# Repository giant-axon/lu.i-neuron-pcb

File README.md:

# Lu.i[¹](#footnote-1) – An educational neuron PCB

Lu.i is an electronic neuron circuit mimicking and illustrating the basic dynamics of real, biological neurons.
The printed circuit board (PCB) features a configurable, fully analog implementation of the leaky integrate-and-fire model and visualizes the internal state, the *membrane potential*, through a VU-meter-style chain of LEDs.
The neuron emits a short pulse whenever the membrane potential crosses a predefined threshold voltage.
Neurons communicate by exchanging these *spikes*.
Multiple boards can be connected via jumper wires to form networks.

<br/>

For a more detailed write-up you may refer to our manuscript:

**Lu. i – A low-cost electronic neuron for education and outreach**  
Yannik Stradmann, Julian Göltz, Mihai A. Petrovici, Johannes Schemmel, Sebastian Billaudelle (2025)  
Trends in Neuroscience and Education, Volume 38, 100248: [10.1016/j.tine.2025.100248](https://doi.org/10.1016/j.tine.2025.100248)

For inquiries feel free to contact us at [info@giantaxon.org](mailto:info@giantaxon.org).

## Features
- fully analog implementation of the leaky integrate-and-fire model
- configurable leak potential and membrane time constant
- three synapses with tunable weight and sign (excitatory or inhibitory) and shared synaptic time constant
- three output terminals to forward spikes to other neurons
- powered by a CR2032 coin battery
- Arduino-compatible (5V-tolerant spike IO)
- VU-meter-style visualization of the membrane potential and spike LED
- optimized for low-cost production (~ 3 € per neuron)

## Example Networks
Resembling the structure of the nervous system, multiple *Lu.i* boards can be connected to form complex neural networks.
They may be used for illustrative purposes, mimicking biological behavior, or even solving functional tasks.
The following hierarchical network, e.g., implements an *exclusive OR* (XOR).

For a more extensive list of example networks please refer to [Lu.i's documentation](doc/).

## Model
The neuron implemented on the PCBs is called Leaky Integrate-and-Fire (LIF) model.
For this model, the membrane voltage follows the dynamics described by the differential equation

$$
    \tau_\text{mem} \frac{\mathrm{d}V_\text{mem}}{\mathrm{d}t} = - \left(V_\text{mem} - V_\text{leak} \right) + I_{\text{syn}} / g_\text{leak}.
$$

In short, the neuron sums up its input $I_\text{syn}$ and decays back to the leak voltage $V_\text{leak}$.
The LIF model, including the spiking behavior when the threshold is reached, is implemented in electric circuits.

## Electronic Implementation
The following circuit diagram shows the different functional blocks of the analog implementation on *Lu.i*.
The full schematics are given as KiCAD design files.

Besides the formation of synaptic connections between the individual neurons, inputs and outputs of each *Lu.i* can also be used to connect with a wide range of microcontrollers and sensors.
Example code can be found in the [documentation](doc/). 

## Manufacturing
The component choice in the *Lu.i* design is optimized for manufacturing at [JLCPCB](https://jlcpcb.com/).
With every [release](../../releases/), we include all the design files necessary for production.
Detailed instructions on the ordering process can be found in the [documentation](doc/).

---

<a name="footnote-1">¹</a> The name »Lu.i« (phonetic notation of »Louis«) is a tribute to Louis E. Lapicque, who first formulated the leaky integrate-and-fire equations modeling the dynamics of a neuron.

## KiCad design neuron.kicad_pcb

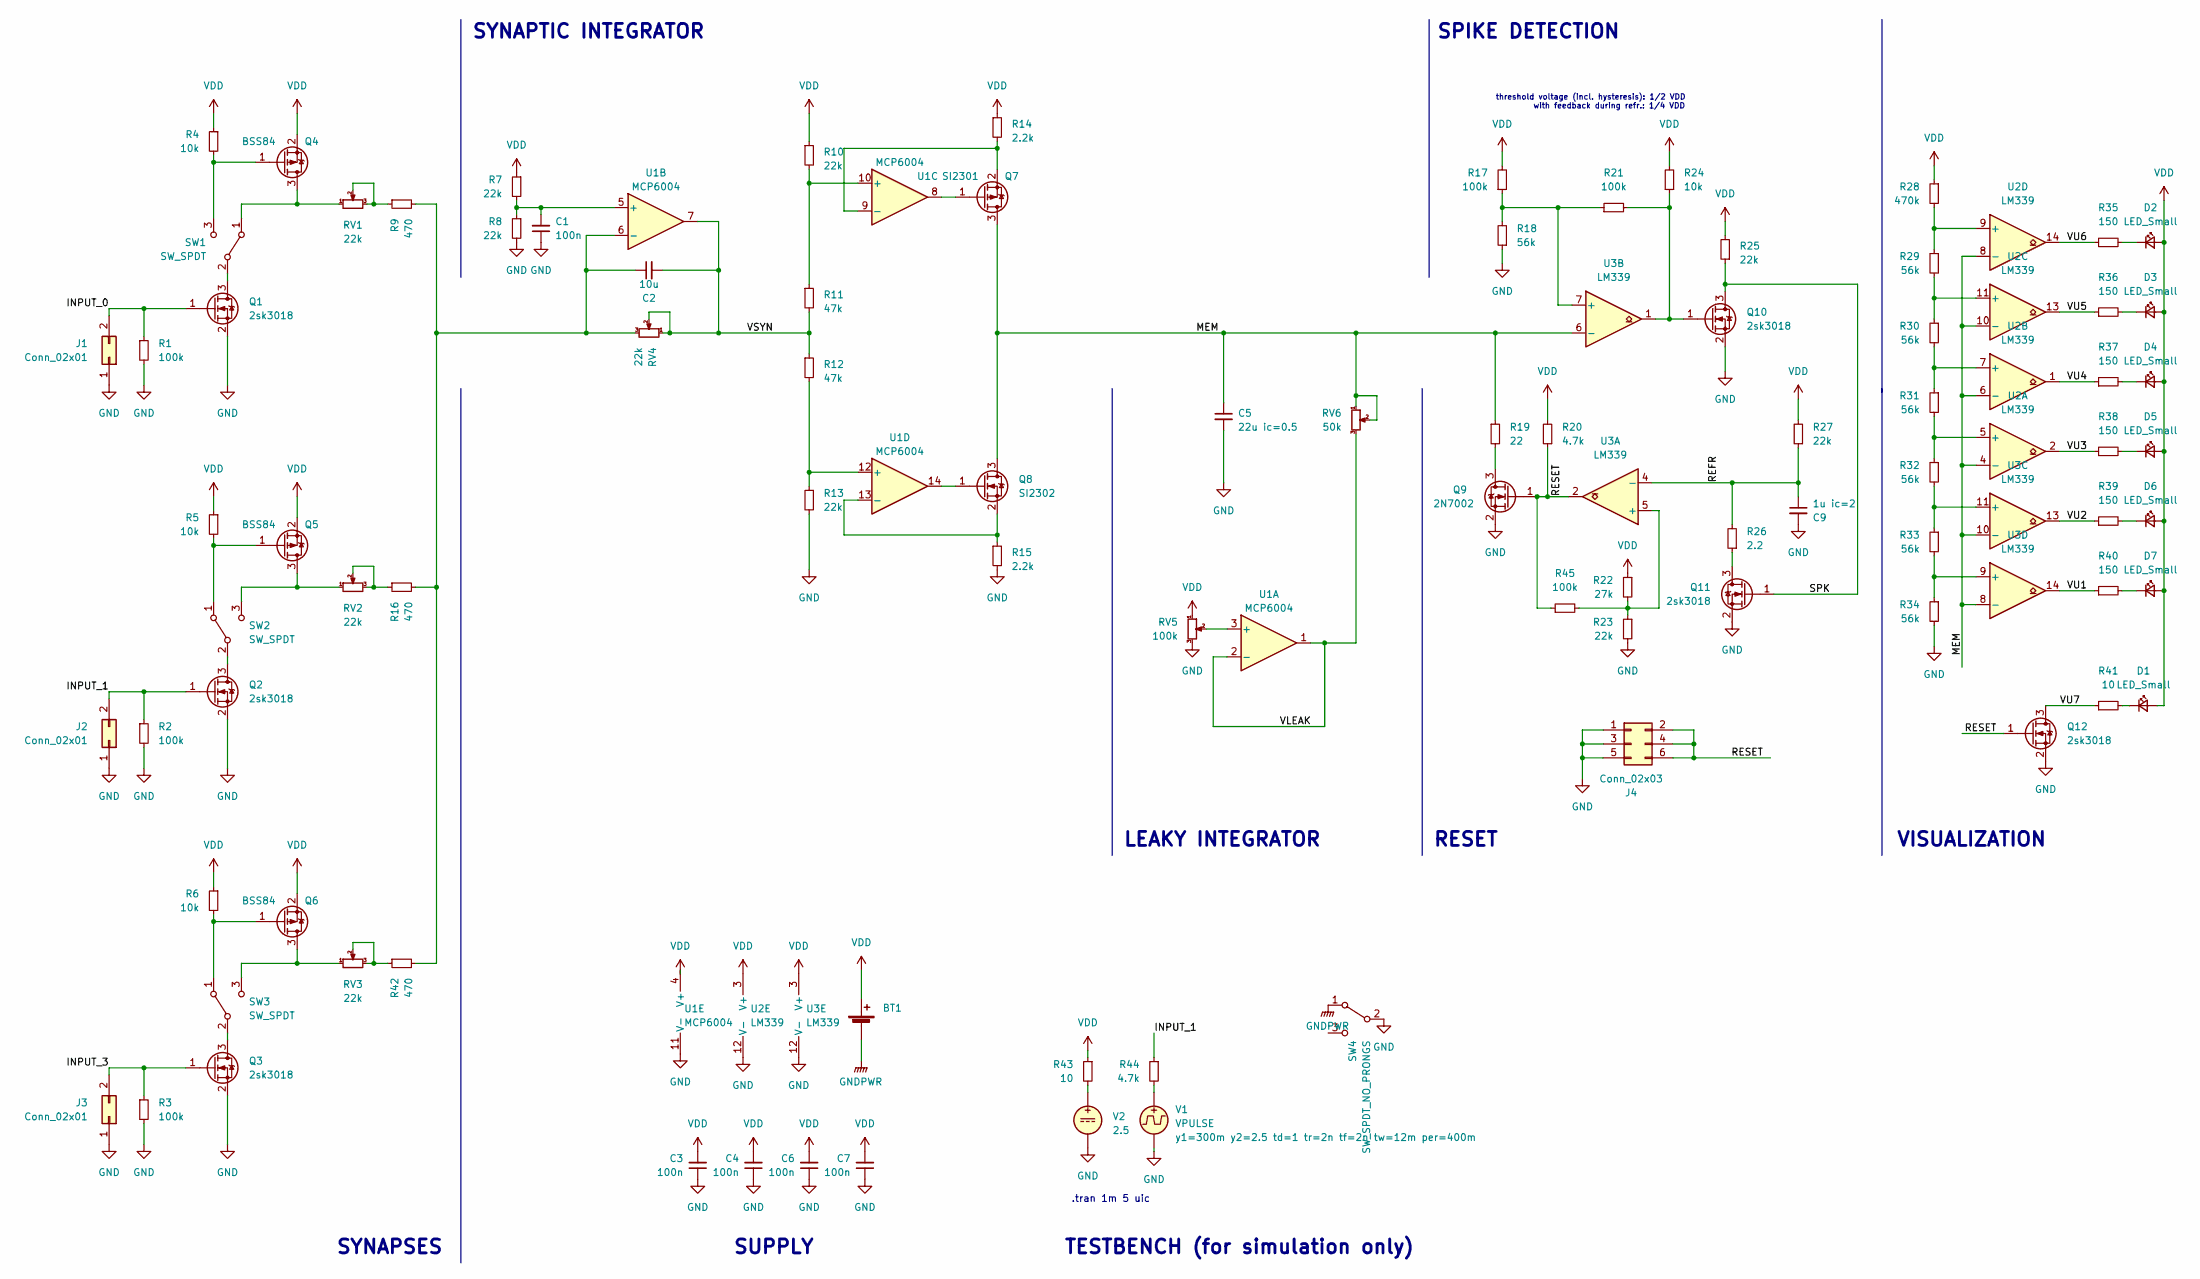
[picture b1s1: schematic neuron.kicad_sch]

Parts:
BT1: type="R" model="Battery_Cell" lib=""; CR2032_Holder; LCSC C70377
C1, C3, C4, C6, C7: 100n; C_0402_1005Metric; LCSC C1525
C2: 10u; C_0402_1005Metric; LCSC C15525
C5: 22u ic=0.5; C_0402_1005Metric; LCSC C415703
C9: 1u ic=2; C_0402_1005Metric; LCSC C52923
D1, D2, D3, D4, D5, D6, D7: LED_Small; LED_0402_1005Metric; LCSC C779450
J1, J2, J3: Conn_02x01; PinHeader_1x02_P2.54mm_Vertical; LCSC C2894925
J4: Conn_02x03; PinHeader_2x03_P2.54mm_Vertical; LCSC C492420
Q1, Q2, Q3, Q10, Q11, Q12: 2sk3018; SOT-23; LCSC C181084
Q4, Q5, Q6: BSS84; SOT-23; LCSC C8492
Q7: SI2301; SOT-23; LCSC C10487
Q8: SI2302; SOT-23; LCSC C10488
Q9: 2N7002; SOT-23; LCSC C8545
R1, R2, R3, R17, R21, R45: 100k; R_0402_1005Metric; LCSC C25741
R4, R5, R6, R24: 10k; R_0402_1005Metric; LCSC C25744
R7, R8, R10, R13: 22k; R_0402_1005Metric; LCSC C326601
R9, R16, R42: 470; R_0402_1005Metric; LCSC C25117
R11, R12: 47k; R_0402_1005Metric; LCSC C5152005
R14, R15: 2.2k; R_0402_1005Metric; LCSC C705646
R18, R29, R30, R31, R32, R33, R34: 56k; R_0402_1005Metric; LCSC C25796
R19: 22; R_0402_1005Metric; LCSC C25092
R20: 4.7k; R_0402_1005Metric; LCSC C25900
R22: 27k; R_0402_1005Metric; LCSC C25771
R23, R25, R27: 22k; R_0402_1005Metric; LCSC C25768
R26: 2.2; R_0402_1005Metric; LCSC C25101
R28: 470k; R_0402_1005Metric; LCSC C25790
R35, R36, R37, R38, R39, R40: 150; R_0402_1005Metric; LCSC C25082
R41: 10; R_0402_1005Metric; LCSC C25077
R43: 10; R_0402_1005Metric; LCSC C25768
R44: 4.7k; R_0402_1005Metric; LCSC C25768
RV1, RV2, RV3, RV4: 22k; Potentiometer; LCSC C128552
RV5: 100k; Potentiometer; LCSC C128545
RV6: 50k; Potentiometer; LCSC C145161
SW1, SW2, SW3: SW_SPDT; K3-1296S-E1; LCSC C128955
SW4: SW_SPDT_NO_PRONGS; SSAJ120100; LCSC C160864
U1: MCP6004; TSSOP-14_4.4x5mm_P0.65mm; LCSC C50282
U2, U3: LM339; TSSOP-14_4.4x5mm_P0.65mm; LCSC C42184
V1: VPULSE
V2: 2.5

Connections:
/INPUT_0: J1.2, Q1.1 (G), R1.1
/INPUT_1: J2.2, Q2.1 (G), R2.1, R44.1
/INPUT_3: J3.2, Q3.1 (G), R3.1
/MEM: C5.1, Q7.3 (D), Q8.3 (D), R19.1, RV6.1, RV6.2, U2.4 (-), U2.6 (-), U2.8 (-), U2.10 (-), U3.6 (-), U3.8 (-), U3.10 (-)
/REFR: C9.1, R26.2, R27.1, U3.4 (-)
/RESET: J4.2, J4.4, J4.6, Q9.1 (G), Q12.1 (G), R20.1, R45.1, U3.2
/SPK: Q10.3 (D), Q11.1 (G), R25.1
/VLEAK: RV6.3, U1.1, U1.2 (-)
/VSYN: C2.2, R11.2, R12.1, RV4.1, RV4.2, U1.7
/VU1: R40.1, U3.14
/VU2: R39.1, U3.13
/VU3: R38.1, U2.2
/VU4: R37.1, U2.1
/VU5: R36.1, U2.13
/VU6: R35.1, U2.14
/VU7: Q12.3 (D), R41.1
GND: C1.1, C3.1, C4.1, C5.2, C6.1, C7.1, C9.2, J1.1, J2.1, J3.1, J4.1, J4.3, J4.5, Q1.2 (S), Q2.2 (S), Q3.2 (S), Q9.2 (S), Q10.2 (S), Q11.2 (S), Q12.2 (S), R1.2, R2.2, R3.2, R8.2, R13.2, R15.2, R18.1, R23.2, R34.2, RV5.3, SW4.2 (B), U1.11 (V-), U2.12 (V-), U3.12 (V-), V1.2, V2.2
GNDPWR: BT1.2 (-), SW4.1 (A)
unnamed: D1.1 (K), R41.2
unnamed: D2.1 (K), R35.2
unnamed: D3.1 (K), R36.2
unnamed: D4.1 (K), R37.2
unnamed: D5.1 (K), R38.2
unnamed: D6.1 (K), R39.2
unnamed: D7.1 (K), R40.2
unnamed: Q1.3 (D), SW1.2 (B)
unnamed: Q2.3 (D), SW2.2 (B)
unnamed: Q3.3 (D), SW3.2 (B)
unnamed: Q4.3 (D), RV1.1, SW1.1 (A)
unnamed: Q4.1 (G), R4.2, SW1.3 (C)
unnamed: Q5.3 (D), RV2.1, SW2.3 (C)
unnamed: Q5.1 (G), R5.2, SW2.1 (A)
unnamed: Q6.3 (D), RV3.1, SW3.3 (C)
unnamed: Q6.1 (G), R6.2, SW3.1 (A)
unnamed: Q7.1 (G), U1.8
unnamed: Q7.2 (S), R14.2, U1.9 (-)
unnamed: Q8.1 (G), U1.14
unnamed: Q8.2 (S), R15.1, U1.13 (-)
unnamed: Q9.3 (D), R19.2
unnamed: Q10.1 (G), R21.2, R24.1, U3.1
unnamed: Q11.3 (D), R26.1
unnamed: R9.1, RV1.2, RV1.3
unnamed: R16.1, RV2.2, RV2.3
unnamed: R42.1, RV3.2, RV3.3
unnamed: R43.2, V2.1
unnamed: R44.2, V1.1
unnamed: RV5.2, U1.3 (+)
unnamed: C1.2, R7.2, R8.1, U1.5 (+)
unnamed: C2.1, R9.2, R16.2, R42.2, RV4.3, U1.6 (-)
unnamed: R10.2, R11.1, U1.10 (+)
unnamed: R12.2, R13.1, U1.12 (+)
unnamed: R31.2, R32.1, U2.5 (+)
unnamed: R30.2, R31.1, U2.7 (+)
unnamed: R29.2, R30.1, U2.11 (+)
unnamed: R28.2, R29.1, U2.9 (+)
unnamed: R22.2, R23.1, R45.2, U3.5 (+)
unnamed: R17.1, R18.2, R21.1, U3.7 (+)
unnamed: R32.2, R33.1, U3.11 (+)
unnamed: R33.2, R34.1, U3.9 (+)
VDD: BT1.1 (+), C3.2, C4.2, C6.2, C7.2, D1.2 (A), D2.2 (A), D3.2 (A), D4.2 (A), D5.2 (A), D6.2 (A), D7.2 (A), Q4.2 (S), Q5.2 (S), Q6.2 (S), R4.1, R5.1, R6.1, R7.1, R10.1, R14.1, R17.2, R20.2, R22.1, R24.2, R25.2, R27.2, R28.1, R43.1, RV5.1, U1.4 (V+), U2.3 (V+), U3.3 (V+)

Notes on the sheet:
LEAKY INTEGRATOR
RESET
SPIKE DETECTION
TESTBENCH (for simulation only)
SYNAPTIC INTEGRATOR
SYNAPSES
SUPPLY
.tran 1m 5 uic
threshold voltage (incl. hysteresis): 1/2 VDD with feedback during refr.: 1/4 VDD
VISUALIZATION

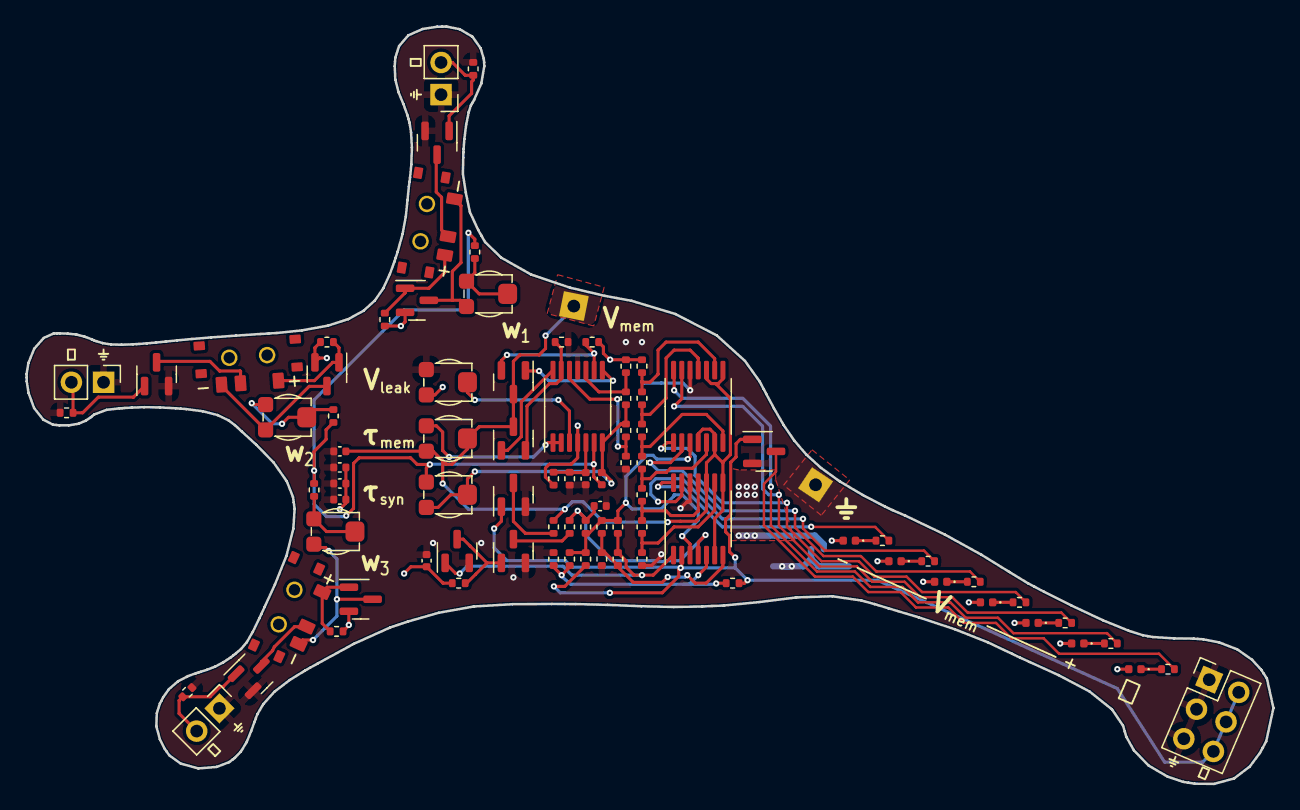
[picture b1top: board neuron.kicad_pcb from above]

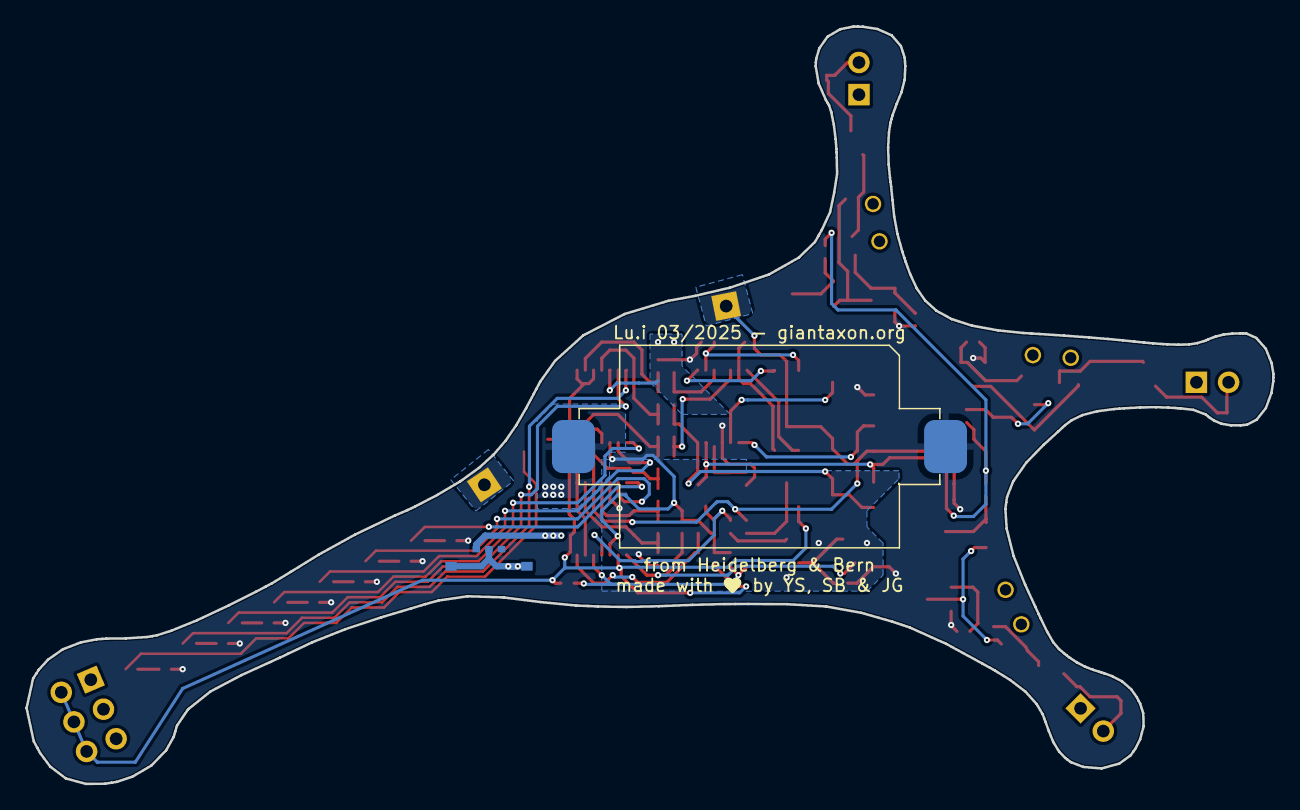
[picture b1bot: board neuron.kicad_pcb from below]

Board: 2 copper layers, 98.5 x 59.8 mm, 88 parts (2 on the bottom side), 58 nets.

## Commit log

2022-09-06 Add photograph
2022-09-06 Crop photograph
2022-09-08 Further compress photograph
2022-09-08 Add animation
2022-09-08 Update animation
2022-09-08 Add animation to README
2022-09-08 neurons in tikz for networks
2022-09-08 synfire chain figure
2022-09-08 improving tikzstyles
2022-09-08 hierarchical tikz network
2022-09-09 add svgs
2022-09-09 added svgs to readme
2022-09-09 adapting svgs
2022-09-09 adapting svgs further
2022-09-10 synfirering
2022-09-16 improve XOR schematic
2022-09-16 use pngs for networks
2022-10-03 Replace animation gif with webp
2022-10-03 Move network figures to new folder
2022-10-03 Add schematic figures
2022-10-03 Move coin photograph to new figure folder
2022-10-03 Add .gitignore for example network sources
2022-10-03 Move example networks to doc
2022-10-03 Fix formatting and image URLs in doc
2022-10-03 Clean up moved files
2022-10-03 Fix URLs of images
2022-10-03 Add back animation.webp
2022-10-03 Remove photograph
2022-10-03 Add differential equation to the Readme
2022-10-03 Add panelized overview schematic figure
2022-10-03 Use overview schematic in README
2022-10-03 Add mail address to README
2022-10-04 Fix schematic LaTeX preamble
2022-10-04 Name (more) components in schematics
2022-10-04 Update schematics according to new sources
2022-10-17 Adapt path to hierarchical network
2023-04-05 Update for second production run
2023-04-05 Migrate to KiCad 7
2023-04-12 Implement exponential synapses
2023-04-12 Update comments in schematic
2023-04-13 Clean up simulation models and testbench
2023-04-13 Clean up schematic
2023-04-13 Update 2N7002 simulation model
2023-05-02 License project under CERN-OHL-S
2023-06-07 Replace synaptic time constant and weight potentiometers by 22k
2023-06-07 Replace membrane capacitor by more common part
2023-06-07 Replace LEDs by more yellow one
2023-07-30 tikzed version
2023-07-30 pdf because png broken
2023-08-04 Change LEDs due to stock shortages
2023-08-04 Annotate board from schematic
2023-08-15 First draft
2023-08-15 add png
2023-08-15 png without lines
2023-11-02 Update README.md
    Add battery type, Spike IO
2024-06-12 Add (optional) power switch on back side
2024-11-18 Update coin photograph
2024-11-18 Update schematic image in Readme
2024-11-18 Update Readme text
2024-11-18 Add documentation for manufacturing
2024-11-18 Adding figure of output trace.
2024-11-18 Add example code for the interaction with microcontrollers
2024-11-19 Improve output_trace figure
2024-11-19 Update lui network preamble
    * from updates in preprint
    * now border-only option
    * VU-meter, as well as switches and tunables
2024-11-19 Update XOR network with new tunables
2024-11-19 Add pngs, pdfs
2024-11-19 Show Jeffress and Ring Attractor
2025-01-14 Add miniposter/stand-up to documentation
2025-02-18 Update publication reference
2025-02-18 Update Readme typesetting
2025-03-31 Migrate to KiCAD 9
2025-03-31 Re-import schematic to PCB
2025-03-31 Add hysteresis for refractory time comparator
2025-03-31 Update layout
